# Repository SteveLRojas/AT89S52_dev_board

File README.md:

# AT89S52_dev_board
Simple development board for AT89S52 microcontrollers

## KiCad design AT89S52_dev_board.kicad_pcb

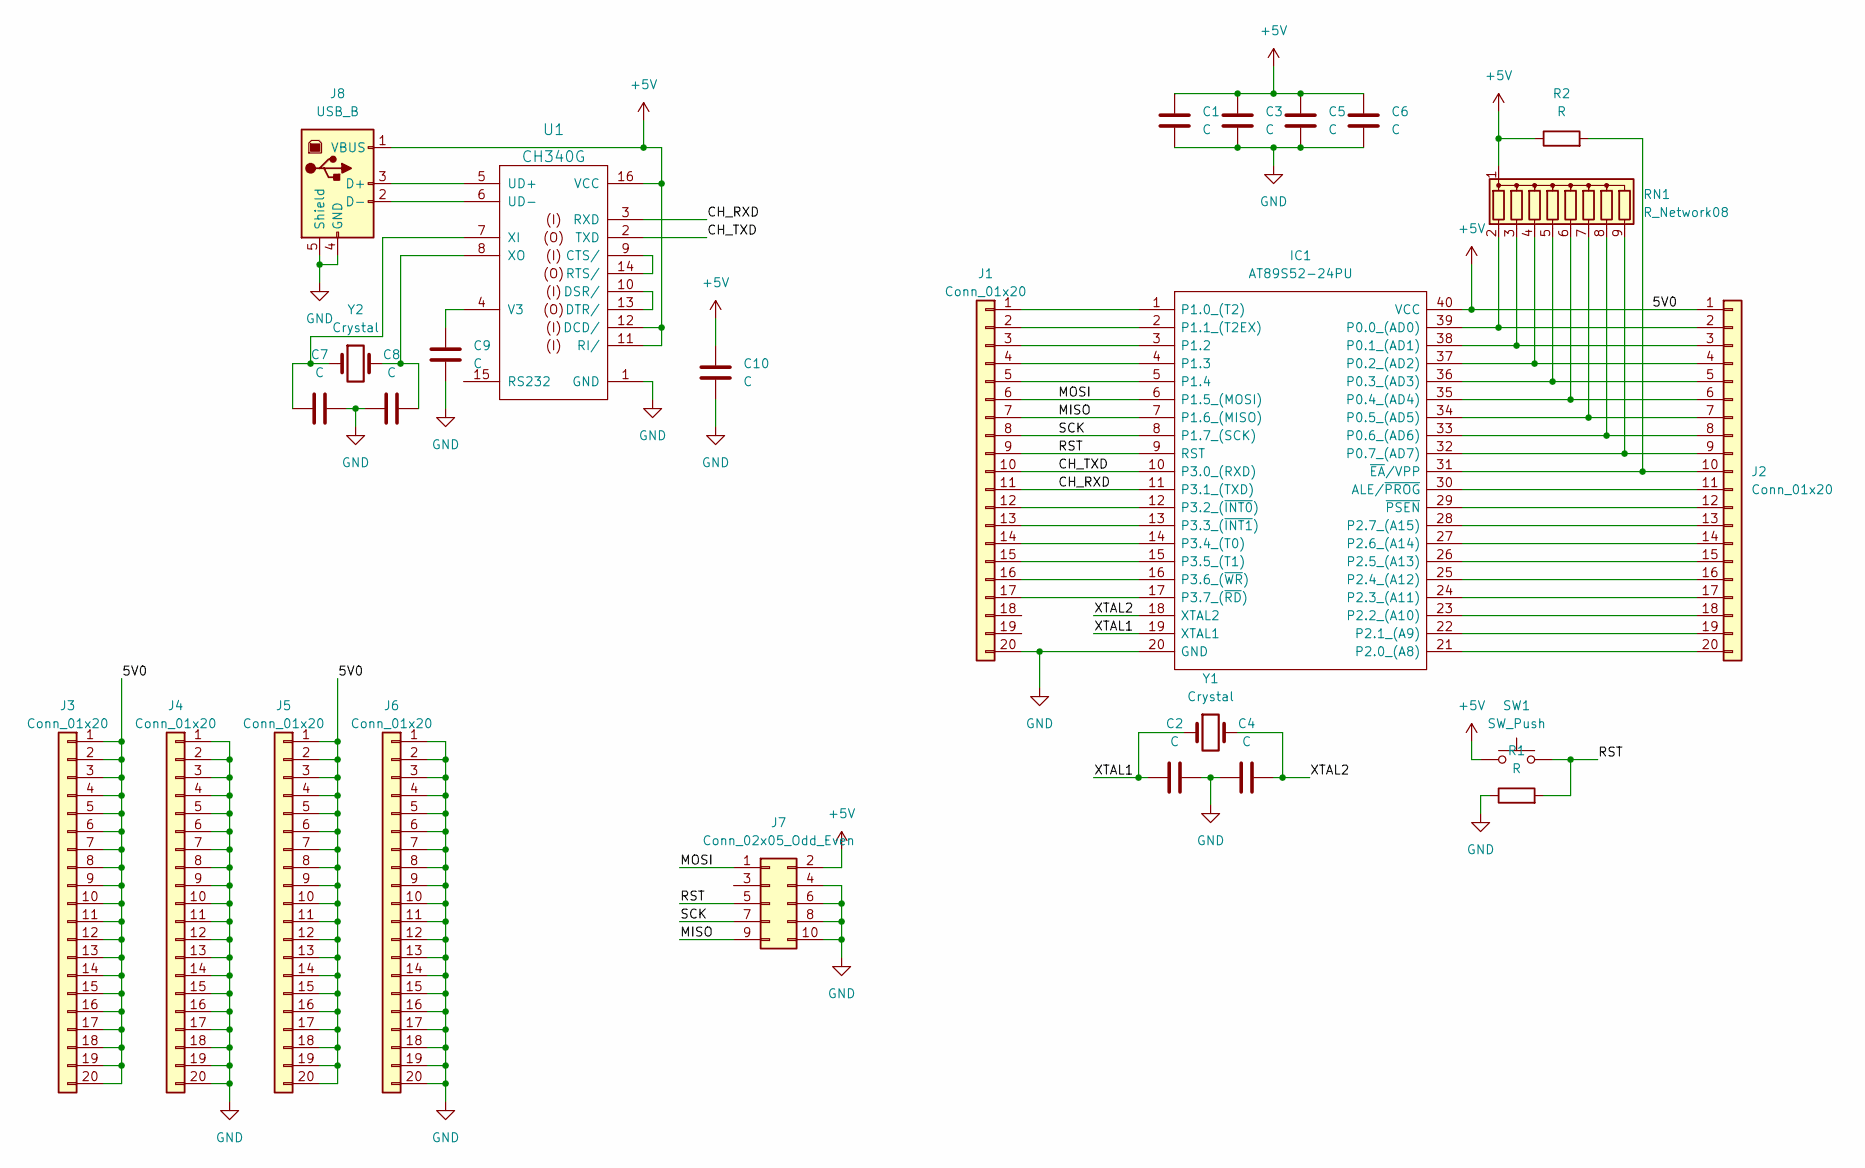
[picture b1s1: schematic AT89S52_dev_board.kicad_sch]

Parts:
C1, C2, C3, C4, C5, C6, C7, C8, C9, C10: C; C_0805_2012Metric
IC1: AT89S52-24PU; DIP1556W56P254L5232H483Q40N; Mouser Part Number 556-A89S52-24PU
J1, J2, J3, J4, J5, J6: Conn_01x20; PinHeader_1x20_P2.54mm_Vertical
J7: Conn_02x05_Odd_Even; IDC-Header_2x05_P2.54mm_Vertical
J8: USB_B; USB_B_OST_USB-B1HSxx_Horizontal
R1, R2: R; R_0805_2012Metric
RN1: R_Network08; R_Array_SIP9
SW1: SW_Push; SW_PUSH_6mm
U1: CH340G; SOP-16_3.9x9.9mm_P1.27mm
Y1, Y2: Crystal; Crystal_HC49-U_Vertical

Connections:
+5V: C1.1, C3.1, C5.1, C6.1, C10.1, IC1.40 (VCC), J2.1, J3.1, J3.2, J3.3, J3.4, J3.5, J3.6, J3.7, J3.8, J3.9, J3.10, J3.11, J3.12, J3.13, J3.14, J3.15, J3.16, J3.17, J3.18, J3.19, J3.20, J5.1, J5.2, J5.3, J5.4, J5.5, J5.6, J5.7, J5.8, J5.9, J5.10, J5.11, J5.12, J5.13, J5.14, J5.15, J5.16, J5.17, J5.18, J5.19, J5.20, J7.2, J8.1 (VBUS), R2.1, RN1.1 (common), SW1.1, U1.11 (RI/), U1.12 (DCD/), U1.16 (VCC)
/CH_RXD: IC1.11 (P3.1_(TXD)), J1.11, U1.3 (RXD)
/CH_TXD: IC1.10 (P3.0_(RXD)), J1.10, U1.2 (TXD)
/MISO: IC1.7 (P1.6_(MISO)), J1.7, J7.9
/MOSI: IC1.6 (P1.5_(MOSI)), J1.6, J7.1
/RST: IC1.9 (RST), J1.9, J7.5, R1.2, SW1.2
/SCK: IC1.8 (P1.7_(SCK)), J1.8, J7.7
/XTAL1: C2.1, IC1.19 (XTAL1), Y1.1
/XTAL2: C4.2, IC1.18 (XTAL2), Y1.2
GND: C1.2, C2.2, C3.2, C4.1, C5.2, C6.2, C7.2, C8.1, C9.2, C10.2, IC1.20 (GND), J1.20, J4.1, J4.2, J4.3, J4.4, J4.5, J4.6, J4.7, J4.8, J4.9, J4.10, J4.11, J4.12, J4.13, J4.14, J4.15, J4.16, J4.17, J4.18, J4.19, J4.20, J6.1, J6.2, J6.3, J6.4, J6.5, J6.6, J6.7, J6.8, J6.9, J6.10, J6.11, J6.12, J6.13, J6.14, J6.15, J6.16, J6.17, J6.18, J6.19, J6.20, J7.4, J7.6, J7.8, J7.10, J8.4 (GND), J8.5 (Shield), R1.1, U1.1 (GND)
unnamed: IC1.1 (P1.0_(T2)), J1.1
unnamed: IC1.2 (P1.1_(T2EX)), J1.2
unnamed: IC1.3 (P1.2), J1.3
unnamed: IC1.4 (P1.3), J1.4
unnamed: IC1.5 (P1.4), J1.5
unnamed: IC1.12 (P3.2_(~INT0)), J1.12
unnamed: IC1.13 (P3.3_(~INT1)), J1.13
unnamed: IC1.14 (P3.4_(T0)), J1.14
unnamed: IC1.15 (P3.5_(T1)), J1.15
unnamed: IC1.16 (P3.6_(~WR)), J1.16
unnamed: IC1.17 (P3.7_(~RD)), J1.17
unnamed: IC1.21 (P2.0_(A8)), J2.20
unnamed: IC1.22 (P2.1_(A9)), J2.19
unnamed: IC1.23 (P2.2_(A10)), J2.18
unnamed: IC1.24 (P2.3_(A11)), J2.17
unnamed: IC1.25 (P2.4_(A12)), J2.16
unnamed: IC1.26 (P2.5_(A13)), J2.15
unnamed: IC1.27 (P2.6_(A14)), J2.14
unnamed: IC1.28 (P2.7_(A15)), J2.13
unnamed: IC1.29 (~PSEN), J2.12
unnamed: IC1.30 (ALE/~PROG), J2.11
unnamed: IC1.31 (~EA/VPP), J2.10, R2.2
unnamed: IC1.32 (P0.7_(AD7)), J2.9, RN1.9 (R8)
unnamed: IC1.33 (P0.6_(AD6)), J2.8, RN1.8 (R7)
unnamed: IC1.34 (P0.5_(AD5)), J2.7, RN1.7 (R6)
unnamed: IC1.35 (P0.4_(AD4)), J2.6, RN1.6 (R5)
unnamed: IC1.36 (P0.3_(AD3)), J2.5, RN1.5 (R4)
unnamed: IC1.37 (P0.2_(AD2)), J2.4, RN1.4 (R3)
unnamed: IC1.38 (P0.1_(AD1)), J2.3, RN1.3 (R2)
unnamed: IC1.39 (P0.0_(AD0)), J2.2, RN1.2 (R1)
unnamed: C9.1, U1.4 (V3)
unnamed: J8.3 (D+), U1.5 (UD+)
unnamed: J8.2 (D-), U1.6 (UD-)
unnamed: C7.1, U1.7 (XI), Y2.1
unnamed: C8.2, U1.8 (XO), Y2.2
unnamed: U1.9 (CTS/), U1.14 (RTS/)
unnamed: U1.10 (DSR/), U1.13 (DTR/)

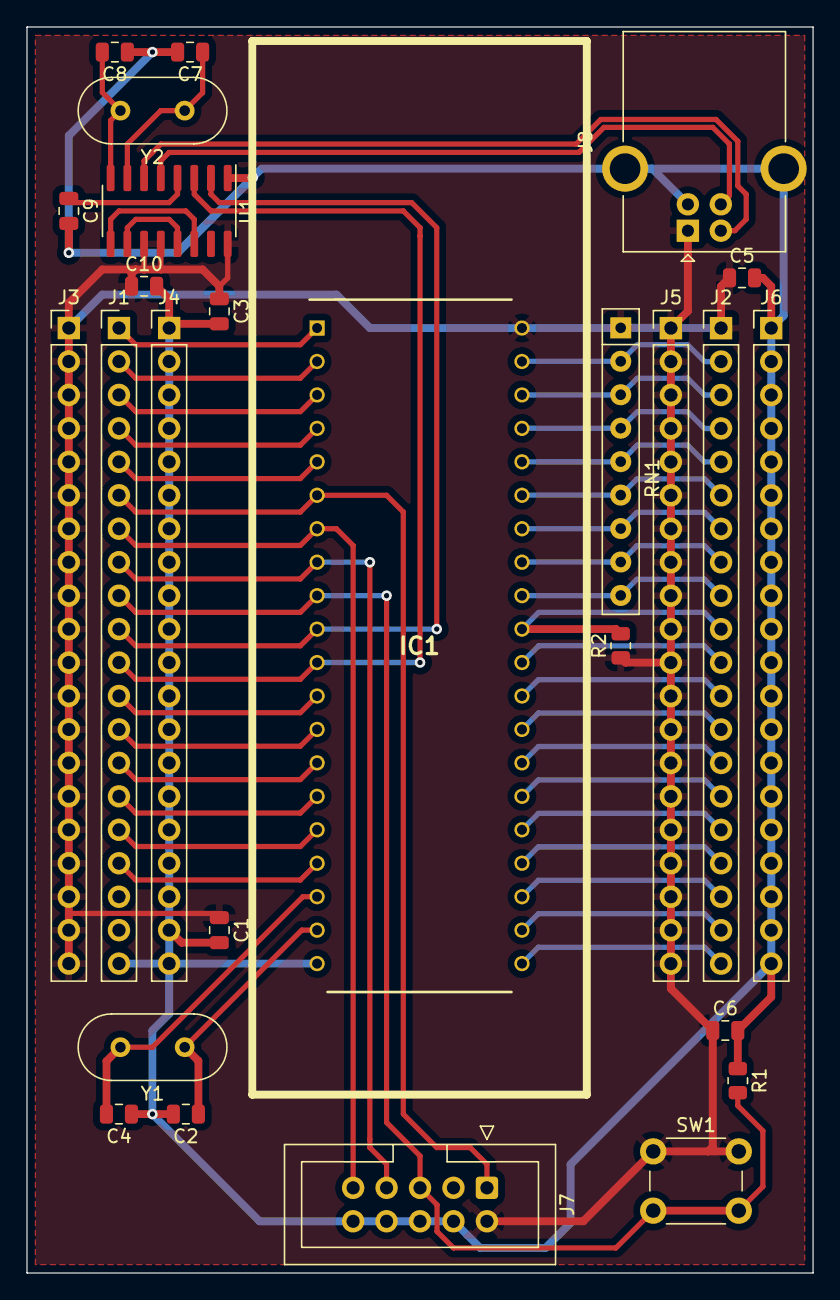
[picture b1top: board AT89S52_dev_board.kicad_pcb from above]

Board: 2 copper layers, 59.7 x 94.6 mm, 26 parts (0 on the bottom side), 47 nets.

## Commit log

2023-01-04 Added gerber files
2023-04-27 Assigned component values
2023-05-17 Added serial example
2023-05-17 Added more examples
2023-05-27 Fixed gerber folder name
2023-06-13 Added datasheets
2023-07-05 Added blinky project
2023-07-06 Added timer based blinky example
2023-07-07 Added interrupt based serial example
2024-01-27 Added BOM and Arduino UMP project
2024-03-03 Workaround for genuine arduino boards (extra bytes inserted when the port is recofigured)
2024-03-03 Added MAX7219 display example
2024-03-03 Added servo example
